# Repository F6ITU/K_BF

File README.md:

# K_BF
OpenHPSDR Audio I/O board, Andromeda/CPU/Hermes interface

K_BF aka Kêtos

This card is an interface between 

- the IDC10 output connector of "audio" signals (HP/headphones, microphone/PTT, CW key) coming from the Andromède board

- the audio input/output jack connectors going to the embedded computer

- the input/output jack connectors of the main SDR board (Hermes/Angelia/Orion) using the OpenHPSDR standard.

Ketos is the name of the sea monster that Perseus slays to deliver Andromeda... 

Andromeda is the high-end "human to machine interface" of the OpenHPSR architecture.

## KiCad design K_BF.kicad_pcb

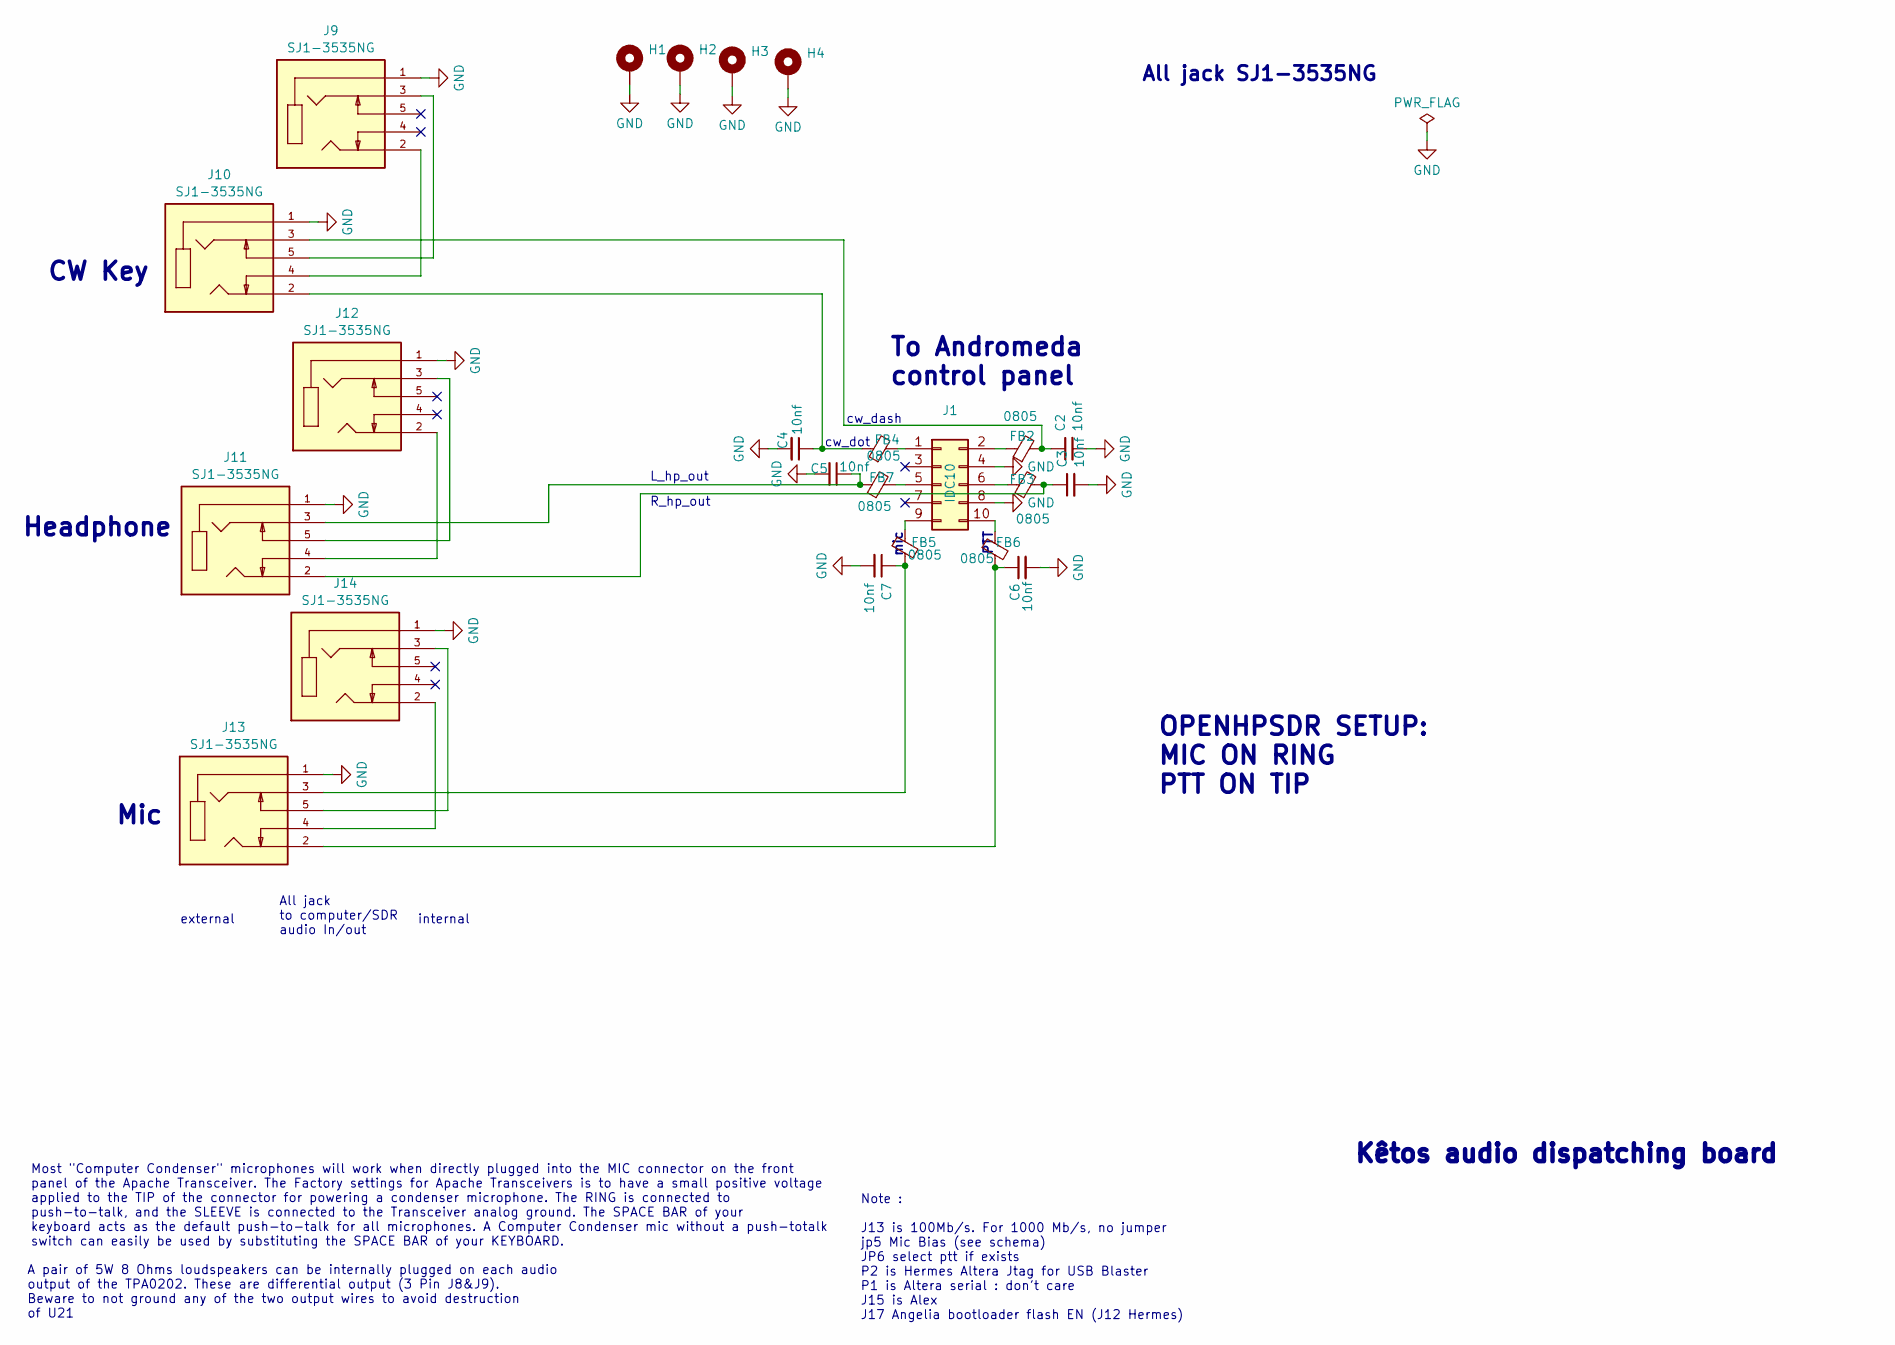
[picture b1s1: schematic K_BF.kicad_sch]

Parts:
C2, C3, C4, C5, C6, C7: 10nf; C_0805_2012Metric_Pad1.18x1.45mm_HandSolder
FB2, FB3, FB4, FB5, FB6, FB7: 0805; L_0805_2012Metric_Pad1.05x1.20mm_HandSolder
H1, H2, H3, H4: MountingHole_Pad; MountingHole_3.5mm_Pad_Via
J1: IDC10; IDC-Header_2x05_P2.54mm_Vertical
J9, J10, J11, J12, J13, J14: SJ1-3535NG; PARTREV 1.02

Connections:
GND: C2.2, C3.2, C4.2, C5.2, C6.2, C7.2, H1.1, H2.1, H3.1, H4.1, J1.4, J1.8, J9.1, J10.1, J11.1, J12.1, J13.1, J14.1
unnamed: C2.1, FB2.2, J10.3
unnamed: C3.1, FB3.2, J11.2
unnamed: C4.1, FB4.1, J10.2
unnamed: C5.1, FB7.1, J11.3
unnamed: C6.1, FB6.2, J13.2
unnamed: C7.1, FB5.2, J13.3
unnamed: FB4.2, J1.1
unnamed: FB2.1, J1.2
unnamed: FB7.2, J1.5
unnamed: FB3.1, J1.6
unnamed: FB5.1, J1.9
unnamed: FB6.1, J1.10
unnamed: J9.2, J10.4
unnamed: J9.3, J10.5
unnamed: J11.4, J12.2
unnamed: J11.5, J12.3
unnamed: J13.4, J14.2
unnamed: J13.5, J14.3

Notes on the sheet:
Kêtos audio dispatching board
internal
Most "Computer Condenser" microphones will work when directly plugged into the MIC connector on the front panel of the Apache Transceiver. The Factory settings for Apache Transceivers is to have a small positive voltage applied to the TIP of the connector for powering a condenser microphone. The RI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
A pair of 5W 8 Ohms loudspeakers can be internally plugged on each audio output of the TPA0202. These are differential output (3 Pin J8&J9). Beware to not ground any of the two output wires to avoid destruction of U21
external
R_hp_out
Headphone
cw_dot
All jack SJ1-3535NG
L_hp_out
Note : J13 is 100Mb/s. For 1000 Mb/s, no jumper jp5 Mic Bias (see schema) JP6 select ptt if exists P2 is Hermes Altera Jtag for USB Blaster P1 is Altera serial : don't care J15 is Alex J17 Angelia bootloader flash EN (J12 Hermes)
OPENHPSDR SETUP: MIC ON RING PTT ON TIP
mic
PTT
To Andromeda control panel
All jack to computer/SDR audio In/out
Mic
CW Key
cw_dash

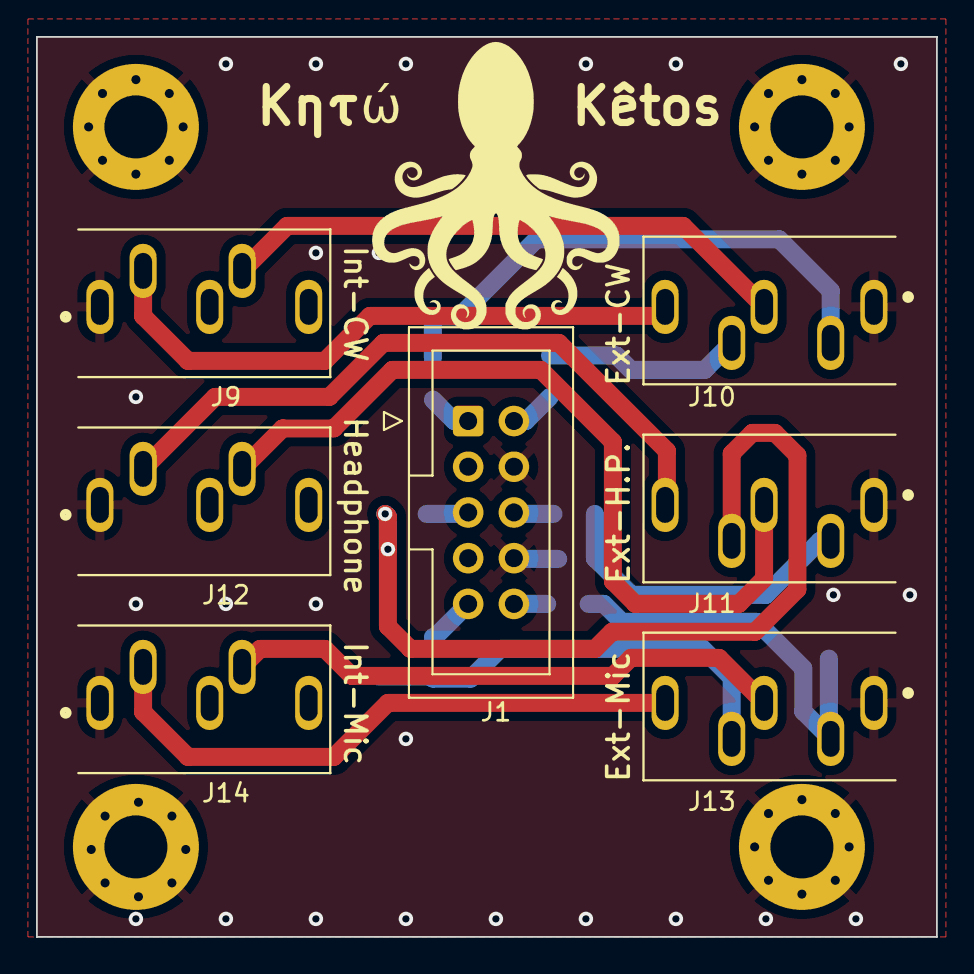
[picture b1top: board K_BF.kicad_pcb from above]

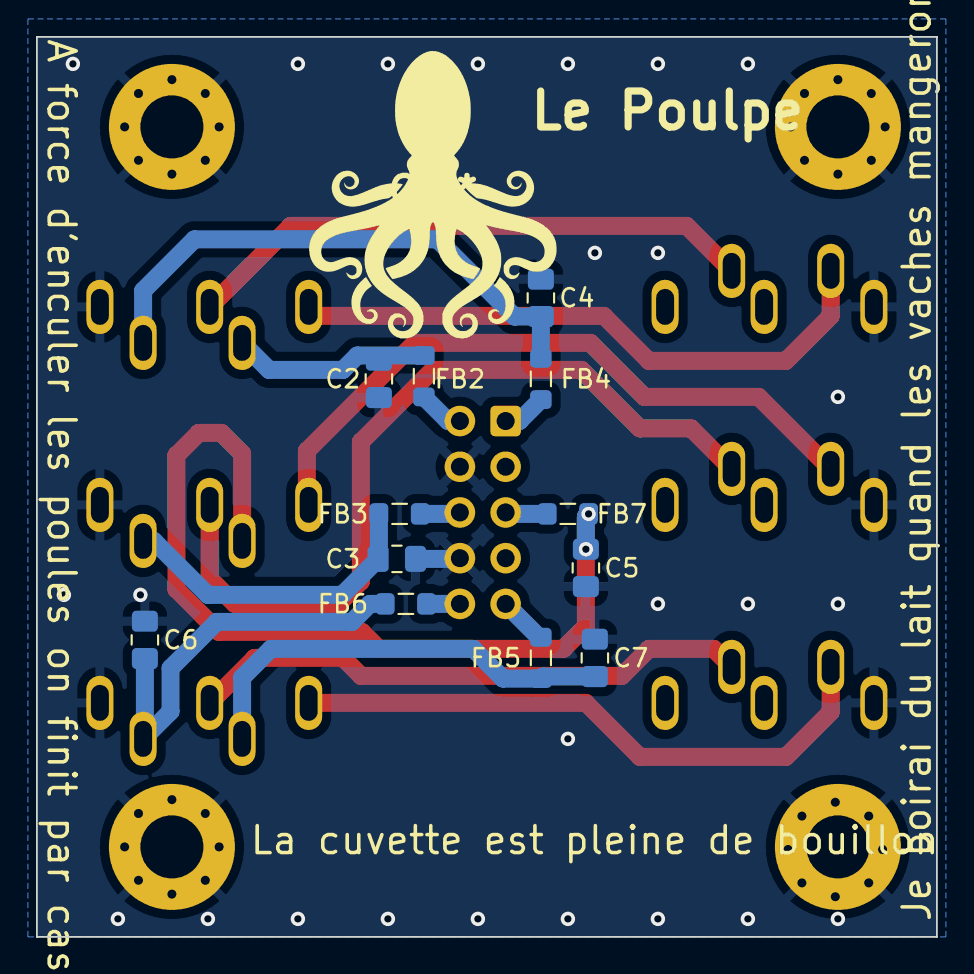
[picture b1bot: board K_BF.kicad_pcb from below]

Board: 2 copper layers, 50.0 x 50.0 mm, 23 parts (12 on the bottom side), 19 nets.

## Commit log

2023-11-04 initial release, no gerber, readme should be translated
2023-11-05 gerber, silk, schematic added
2023-11-05 new readme, 3D capture added
